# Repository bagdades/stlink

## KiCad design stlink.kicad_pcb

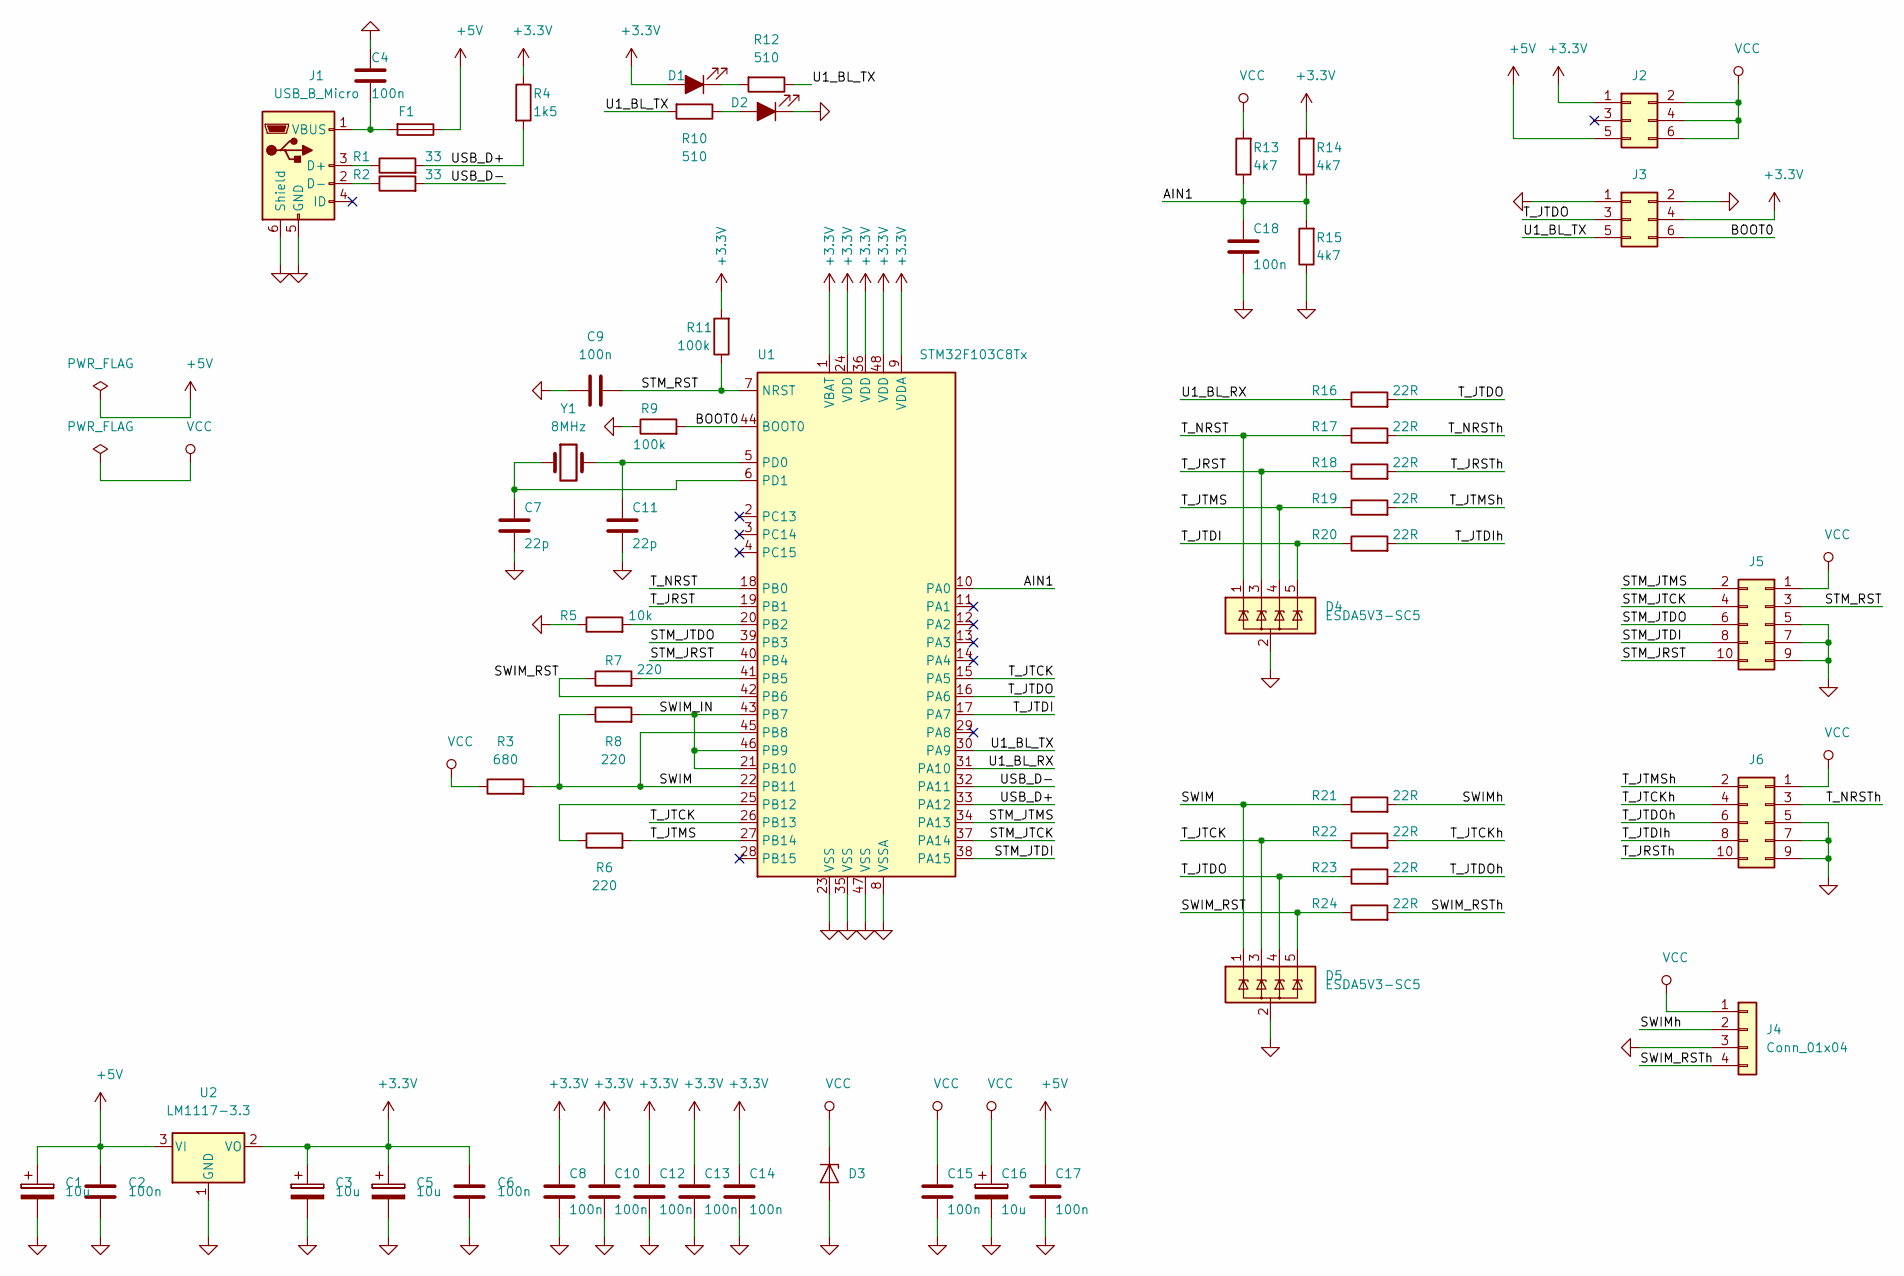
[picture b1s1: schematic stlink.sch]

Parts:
C1, C3, C5, C16: 10u; CP_EIA-3528-21_Kemet-B
C2, C4, C6, C8, C9, C10, C12, C13, C14, C15, C17, C18: 100n; C_0603_1608Metric
C7, C11: 22p; C_0603_1608Metric
D1, D2: LED_ALT; LED_D3.0mm
D3: D_Zener; D_MiniMELF
D4, D5: ESDA5V3-SC5; SOT-23-5
F1: Fuse; Fuse_1206_3216Metric
J1: USB_B_Micro; USB_Micro-B_Molex_47346-0001
J2, J3: Conn_02x03_Odd_Even; PinHeader_2x03_P2.54mm_Vertical
J4: Conn_01x04; JST_PH_S4B-PH-K_1x04_P2.00mm_Horizontal
J5, J6: Conn_02x05_Odd_Even; IDC-Header_2x05_P2.54mm_Vertical
R1, R2: 33; R_0603_1608Metric
R3: 680; R_0603_1608Metric
R4: 1k5; R_0603_1608Metric
R5: 10k; R_0603_1608Metric
R6, R7, R8: 220; R_0603_1608Metric
R9, R11: 100k; R_0603_1608Metric
R10, R12: 510; R_0603_1608Metric
R13, R14, R15: 4k7; R_0603_1608Metric
R16, R17, R18, R19, R20, R21, R22, R23, R24: 22R; R_0603_1608Metric
U1: STM32F103C8Tx; LQFP-48_7x7mm_P0.5mm
U2: LM1117-3.3; SOT-223-3_TabPin2
Y1: 8MHz; Crystal_HC49-4H_Vertical

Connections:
+3V3: C3.1, C5.1, C6.1, C8.1, C10.1, C12.1, C13.1, C14.1, D1.2 (A), J2.1, J3.4, R4.1, R11.2, R14.2, U1.1 (VBAT), U1.9 (VDDA), U1.24 (VDD), U1.36 (VDD), U1.48 (VDD), U2.2 (VO)
+5V: C1.1, C2.1, C17.1, F1.1, J2.5, U2.3 (VI)
/AIN1: C18.2, R13.1, R14.1, R15.2, U1.10 (PA0)
/BOOT0: J3.6, R9.2, U1.44 (BOOT0)
/STM_JRST: J5.10, U1.40 (PB4)
/STM_JTCK: J5.4, U1.37 (PA14)
/STM_JTDI: J5.8, U1.38 (PA15)
/STM_JTDO: J5.6, U1.39 (PB3)
/STM_JTMS: J5.2, U1.34 (PA13)
/STM_RST: C9.1, J5.3, R11.1, U1.7 (NRST)
/SWIM: D5.1 (IO1), R3.2, R8.1, R21.1, U1.22 (PB11), U1.45 (PB8)
/SWIM_IN: R8.2, U1.21 (PB10), U1.43 (PB7), U1.46 (PB9)
/SWIM_RST: D5.5 (IO4), R7.1, R24.1, U1.42 (PB6)
/SWIM_RSTh: J4.4, R24.2
/SWIMh: J4.2, R21.2
/T_JRST: D4.3 (IO2), R18.1, U1.19 (PB1)
/T_JRSTh: J6.10, R18.2
/T_JTCK: D5.3 (IO2), R22.1, U1.15 (PA5), U1.26 (PB13)
/T_JTCKh: J6.4, R22.2
/T_JTDI: D4.5 (IO4), R20.1, U1.17 (PA7)
/T_JTDIh: J6.8, R20.2
/T_JTDO: D5.4 (IO3), J3.3, R16.2, R23.1, U1.16 (PA6)
/T_JTDOh: J6.6, R23.2
/T_JTMS: D4.4 (IO3), R6.2, R19.1, U1.27 (PB14)
/T_JTMSh: J6.2, R19.2
/T_NRST: D4.1 (IO1), R17.1, U1.18 (PB0)
/T_NRSTh: J6.3, R17.2
/U1_BL_RX: R16.1, U1.31 (PA10)
/U1_BL_TX: J3.5, R10.2, R12.1, U1.30 (PA9)
/USB_D+: R1.2, R4.2, U1.33 (PA12)
/USB_D-: R2.2, U1.32 (PA11)
GND: C1.2, C2.2, C3.2, C4.2, C5.2, C6.2, C7.2, C8.2, C9.2, C10.2, C11.2, C12.2, C13.2, C14.2, C15.2, C16.2, C17.2, C18.1, D2.1 (K), D3.2 (A), D4.2 (GND), D5.2 (GND), J1.5 (GND), J1.6 (Shield), J3.1, J3.2, J4.3, J5.5, J5.7, J5.9, J6.5, J6.7, J6.9, R5.1, R9.1, R15.1, U1.8 (VSSA), U1.23 (VSS), U1.35 (VSS), U1.47 (VSS), U2.1 (GND)
unnamed: C4.1, F1.2, J1.1 (VBUS)
unnamed: C7.1, U1.6 (PD1), Y1.1
unnamed: C11.1, U1.5 (PD0), Y1.2
unnamed: D1.1 (K), R12.2
unnamed: D2.2 (A), R10.1
unnamed: J1.2 (D-), R2.1
unnamed: J1.3 (D+), R1.1
unnamed: R5.2, U1.20 (PB2)
unnamed: R6.1, U1.25 (PB12)
unnamed: R7.2, U1.41 (PB5)
VCC: C15.1, C16.1, D3.1 (K), J2.2, J2.4, J2.6, J4.1, J5.1, J6.1, R3.1, R13.2

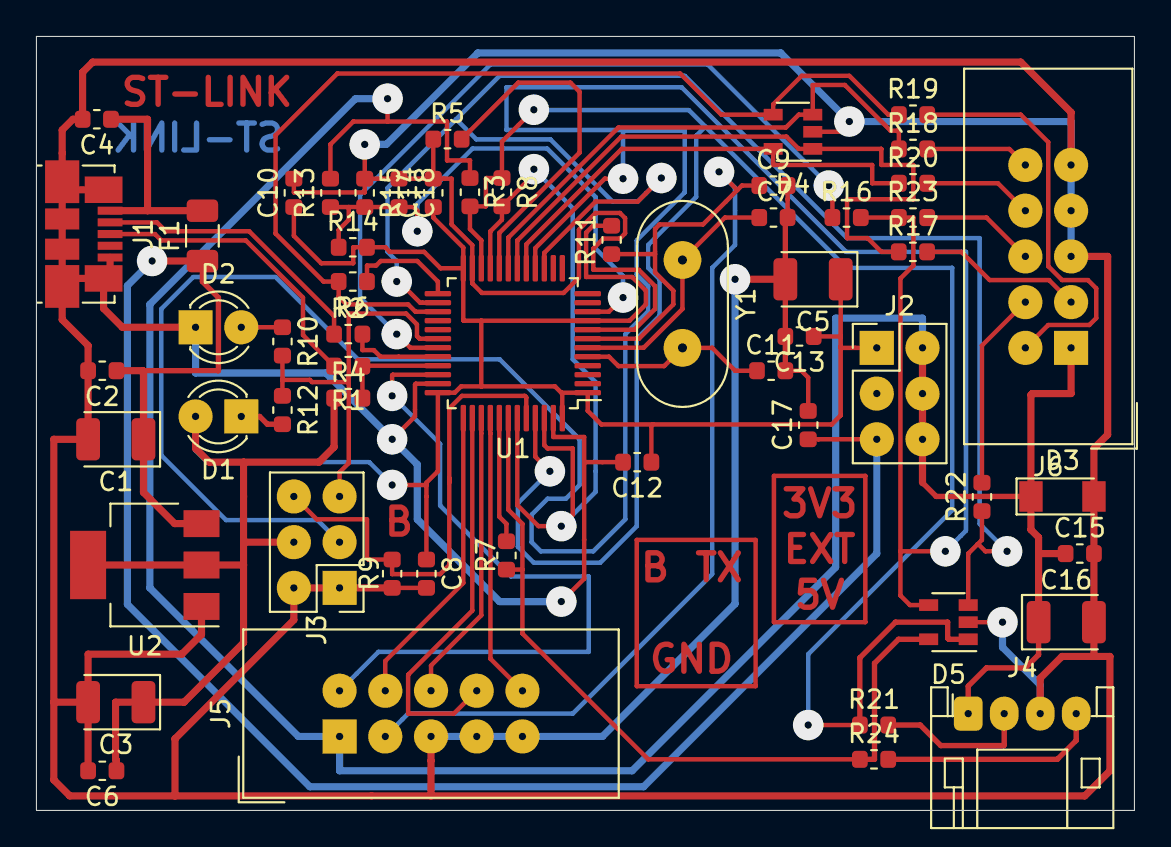
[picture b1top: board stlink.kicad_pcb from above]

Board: 2 copper layers, 61.0 x 43.0 mm, 57 parts (0 on the bottom side), 43 nets.
